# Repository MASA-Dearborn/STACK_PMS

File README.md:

# PMS
Power Management System board
STACK_PMS

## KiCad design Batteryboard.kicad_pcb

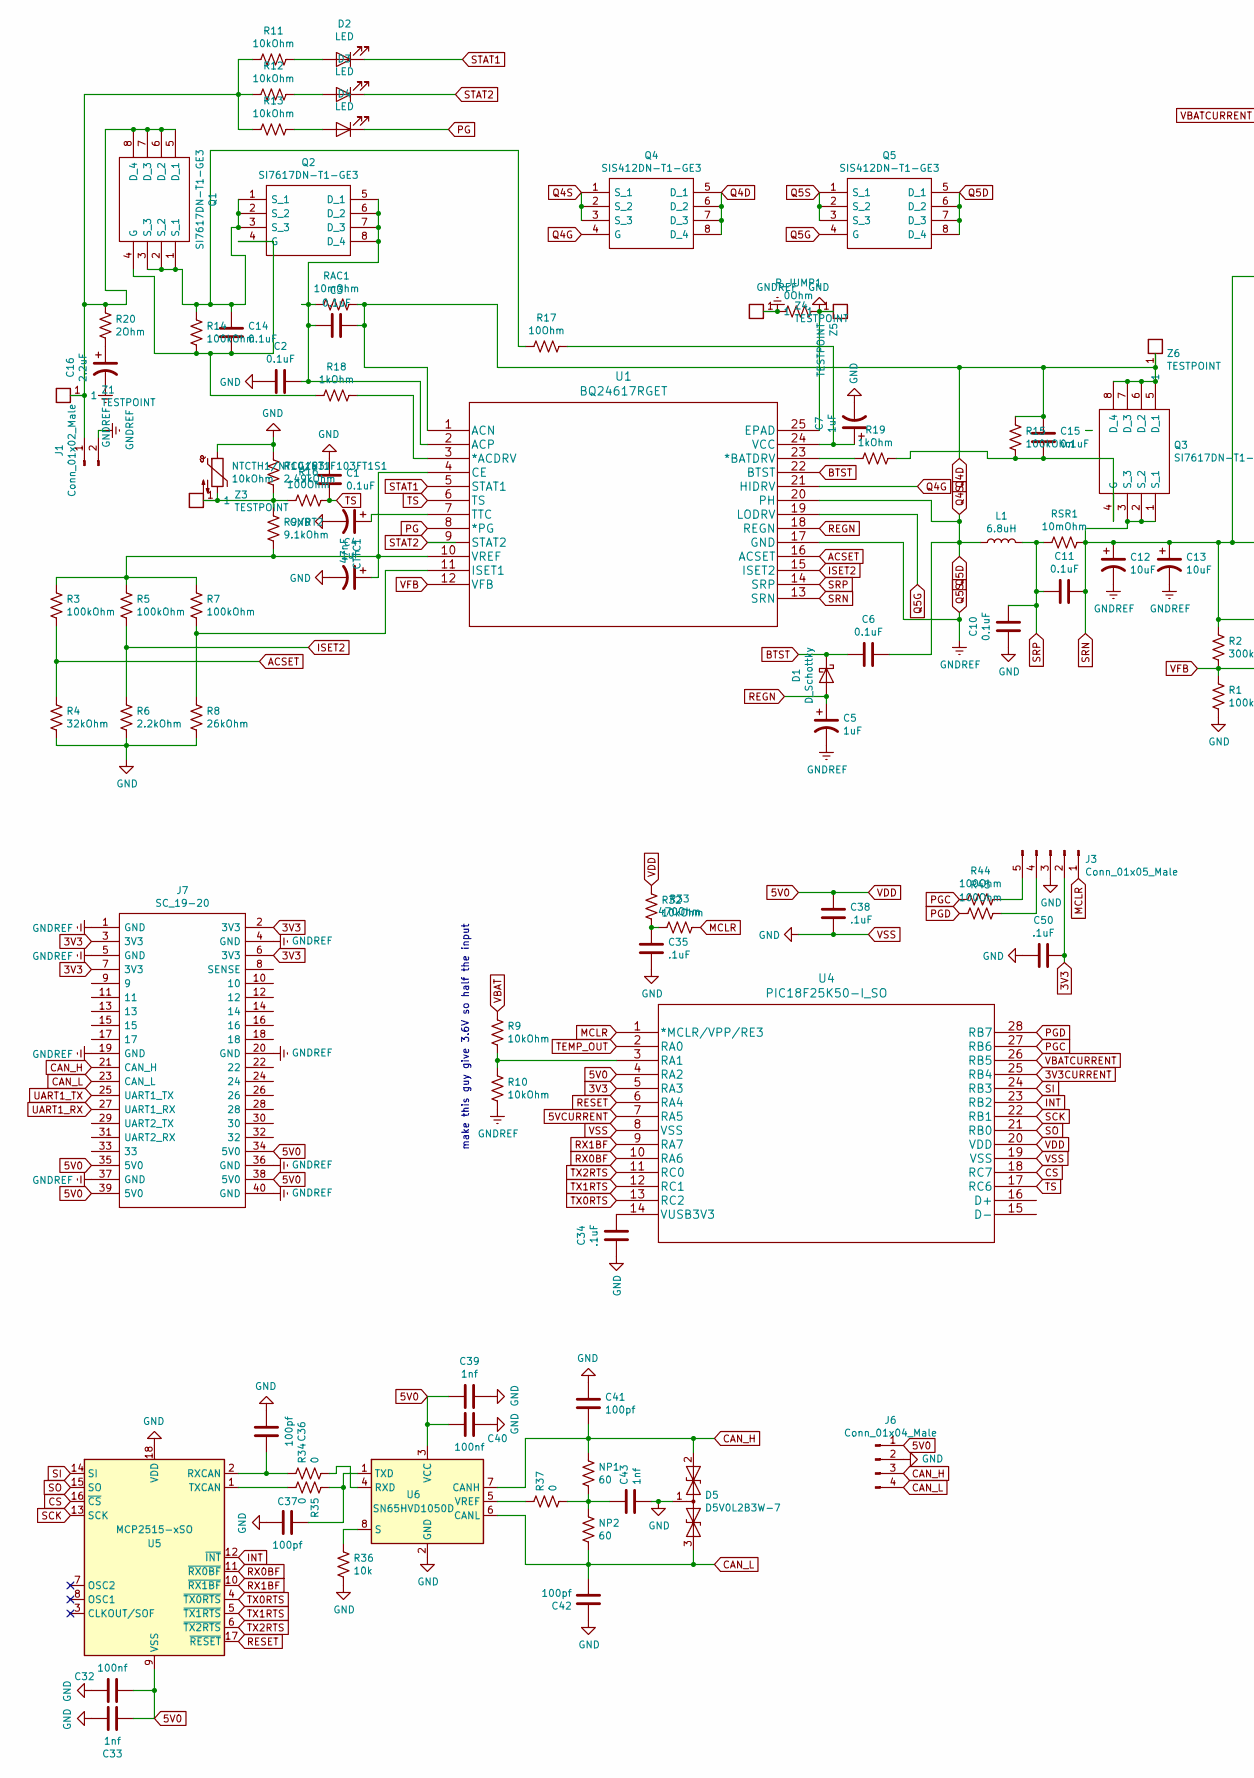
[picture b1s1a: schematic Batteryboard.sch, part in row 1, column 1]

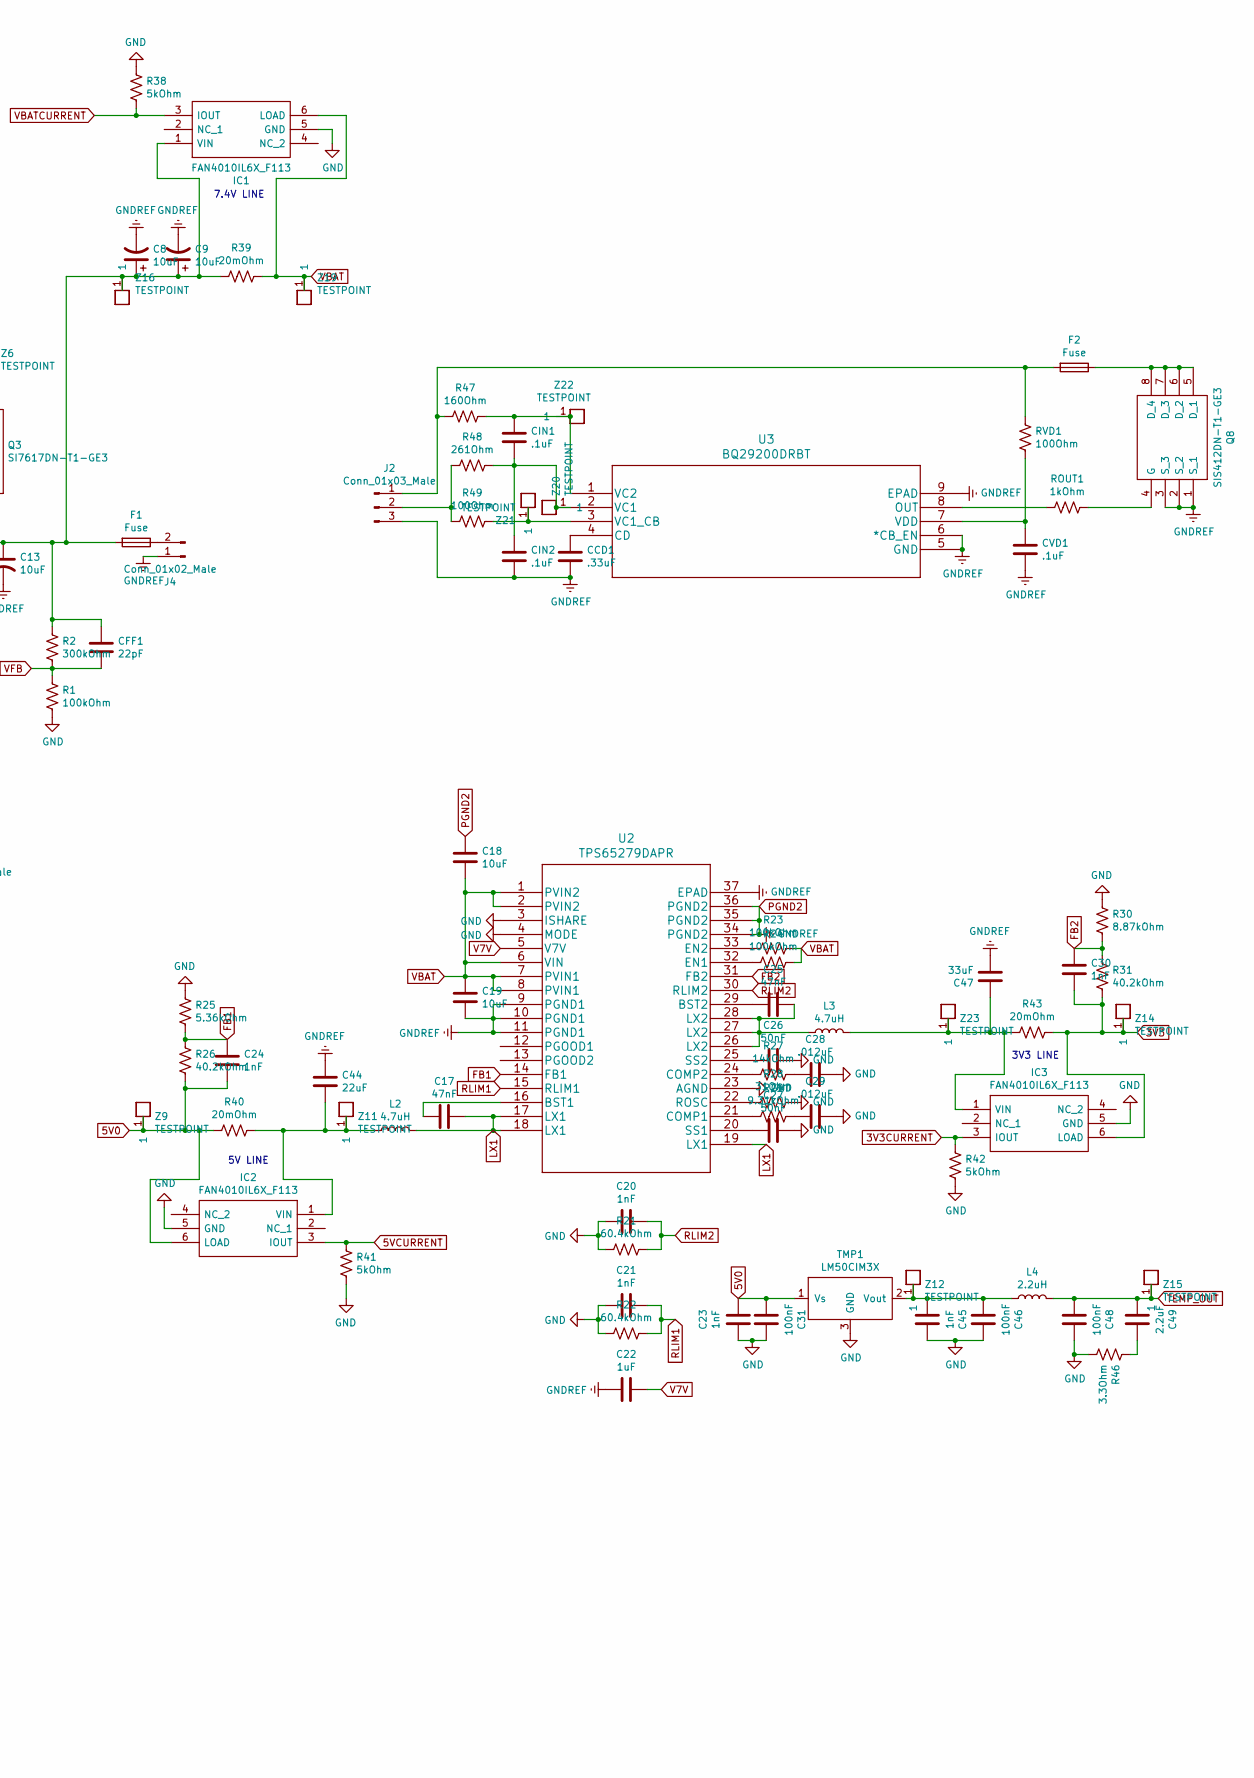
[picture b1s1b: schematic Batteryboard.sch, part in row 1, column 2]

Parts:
C1, C2, C3, C6, C10, C11, C14, C15: 0.1uF; C_0603_1608Metric
C4, C5, C7, C22: 1uF; C_0603_1608Metric
C8, C9, C12, C13, C18, C19: 10uF; C_0603_1608Metric
C16, C49: 2.2uF; C_0603_1608Metric
C17, C25: 47nF; C_0603_1608Metric
C20, C21, C23, C24, C30, C45: 1nF; C_0603_1608Metric
C26, C27: 50nF; C_0603_1608Metric
C28, C29: .012uF; C_0603_1608Metric
C31, C46, C48: 100nF; C_0603_1608Metric
C32, C40: 100nf; C_0603_1608Metric
C33, C39, C43: 1nf; C_0603_1608Metric
C34, C35, C38, C50: .1uF; C_0603_1608Metric
C36, C37, C41, C42: 100pf; C_0603_1608Metric
C44: 22uF; C_0603_1608Metric
C47: 33uF; C_0805_2012Metric
CCD1: .33uF; C_0603_1608Metric
CFF1: 22pF; C_0603_1608Metric
CIN1, CIN2: .1uF; C_0603_1608Metric
CTTC1: 47nF; C_0603_1608Metric
CVD1: .1uF; C_0603_1608Metric
D1: D_Schottky; D_SOD-323
D2, D3, D4: LED; D_0603_1608Metric
D5: D5V0L2B3W-7; SOT-23
F1, F2: Fuse; Fuseholder_Blade_Mini_Keystone_3557-2
IC1, IC2, IC3: FAN4010IL6X_F113; 6-LEAD_MICROPAK; Manufacturer_Part_Number FAN4010IL6X_F113; Mouser Part Number 512-FAN4010IL6X_F113
J1, J4: Conn_01x02_Male; 1-1123723-2
J2: Conn_01x03_Male; JST_XH_B3B-XH-AM_1x03_P2.50mm_Vertical
J3: Conn_01x05_Male; PinHeader_1x05_P2.54mm_Vertical
J6: Conn_01x04_Male; 1734595-4
J7: SC_19-20; Stack_Connector_2019_2020; Manufacturer_Part_Number TFC-120-32-F-D-A-K-TR
L1: 6.8uH; L_Vishay_IHLP-2525
L2, L3: 4.7uH; SRP7030-4R7M
L4: 2.2uH; L_0603_1608Metric
NP1, NP2: 60; R_0603_1608Metric
NTCTH1/NTCG163JF103FT1S1: 10kOhm; R_0603_1608Metric
Q1, Q2, Q3: SI7617DN-T1-GE3; SIS862DNT1GE3; Mouser Part Number 781-SI7617DN-GE3
Q4, Q5, Q8: SIS412DN-T1-GE3; SIS862DNT1GE3; Mouser Part Number 781-SI7617DN-GE3
R1, R3, R5, R7, R14, R15, R23, R24: 100kOhm; R_0603_1608Metric
R2: 300kOhm; R_0603_1608Metric
R4: 32kOhm; R_0603_1608Metric
R6: 2.2kOhm; R_0603_1608Metric
R8: 26kOhm; R_0603_1608Metric
R9, R10, R11, R12, R13, R32: 10kOhm; R_0603_1608Metric
R9/RT2: 9.1kOhm; R_0603_1608Metric
R10/RT1: 2.49kOhm; R_0603_1608Metric
R16, R44, R45, R49: 100Ohm; R_0603_1608Metric
R17: 10Ohm; R_0603_1608Metric
R18, R19: 1kOhm; R_0603_1608Metric
R20: 2Ohm; R_0603_1608Metric
R21, R22: 60.4kOhm; R_0603_1608Metric
R25: 5.36kOhm; R_0603_1608Metric
R26, R31: 40.2kOhm; R_0603_1608Metric
R27: 14kOhm; R_0603_1608Metric
R28: 31Ohm; R_0603_1608Metric
R29: 9.31kOhm; R_0603_1608Metric
R30: 8.87kOhm; R_0603_1608Metric
R33: 470Ohm; R_0603_1608Metric
R34, R35, R37: 0; R_0603_1608Metric
R36: 10k; R_0603_1608Metric
R38, R41, R42: 5kOhm; R_0603_1608Metric
R39, R40, R43: 20mOhm; R_0603_1608Metric
R46: 3.3Ohm; R_0603_1608Metric
R47: 160Ohm; R_0603_1608Metric
R48: 261Ohm; R_0603_1608Metric
RAC1: 10mOhm; R_0603_1608Metric
ROUT1: 1kOhm; R_0603_1608Metric
RSR1: 10mOhm; R_0603_1608Metric
RVD1: 100Ohm; R_0603_1608Metric
R_JUMP1: 0Ohm; R_0603_1608Metric
TMP1: LM50CIM3X; SOT-23
U1: BQ24617RGET
U2: TPS65279DAPR
U3: BQ29200DRBT
U4: PIC18F25K50-I_SO; PIC18F25K50-I&slash_SO
U5: MCP2515-xSO; SOIC-18W_7.5x11.6mm_P1.27mm
U6: SN65HVD1050D; SOIC-8_3.9x4.9mm_P1.27mm
Z1, Z3, Z4, Z5, Z6, Z9, Z11, Z12, Z14, Z15, Z16, Z19, Z20, Z21, Z22, Z23: TESTPOINT

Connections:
3V3: C30.2, C50.1, IC3.6 (LOAD), J3.2, J7.2 (3V3), J7.3 (3V3), J7.6 (3V3), J7.7 (3V3), R31.2, R43.1, U4.5 (RA3), Z14.1
3V3CURRENT: IC3.3 (IOUT), R42.1, U4.25 (RB4)
5V0: C23.1, C24.2, C31.2, C32.1, C33.2, C38.1, C39.2, C40.1, IC2.6 (LOAD), J6.1, J7.34 (5V0), J7.35 (5V0), J7.38 (5V0), J7.39 (5V0), R26.2, R32.1, R40.2, TMP1.1 (Vs), U4.4 (RA2), U4.20 (VDD), U5.9 (VSS), U6.3 (VCC), Z9.1
5VCURRENT: IC2.3 (IOUT), R41.1, U4.7 (RA5)
ACSET: R3.2, R4.1, U1.16 (ACSET)
BTST: C6.2, D1.1 (K), U1.22 (BTST)
CAN_H: C41.2, D5.2 (A1), J6.3, J7.21 (CAN_H), NP1.1, U6.7 (CANH)
CAN_L: C42.2, D5.3 (A2), J6.4, J7.23 (CAN_L), NP2.2, U6.6 (CANL)
CS: U4.18 (RC7), U5.16 (~CS)
FB1: C24.1, R25.2, R26.1, U2.14 (FB1)
FB2: C30.1, R30.2, R31.1, U2.31 (FB2)
INT: U4.23 (RB2), U5.12 (~INT)
ISET2: R5.2, R6.1, U1.15 (ISET2)
LX1: C17.1, L2.2, U2.17 (LX1), U2.18 (LX1), U2.19 (LX1)
MCLR: J3.1, R33.2, U4.1 (*MCLR/VPP/RE3)
unnamed: C2.1, C3.2, Q2.5 (D_1), Q2.6 (D_2), Q2.7 (D_3), Q2.8 (D_4), RAC1.2, U1.2 (ACP)
unnamed: C4.1, R3.1, R5.1, R7.1, R9/RT2.2, U1.4 (CE), U1.10 (VREF)
unnamed: C7.1, R17.1, U1.24 (VCC)
unnamed: C14.1, Q1.1 (S_1), Q1.2 (S_2), Q1.3 (S_3), Q2.1 (S_1), Q2.2 (S_2), Q2.3 (S_3), R14.1, R17.2
unnamed: C14.2, Q1.4 (G), Q2.4 (G), R14.2, R18.2
unnamed: C15.2, Q3.4 (G), R15.2, R19.1
unnamed: C16.1, R20.2
unnamed: C17.2, U2.16 (BST1)
unnamed: C25.1, L3.1, U2.26 (LX2), U2.27 (LX2), U2.28 (LX2)
unnamed: C25.2, U2.29 (BST2)
unnamed: C26.2, U2.25 (SS2)
unnamed: C27.2, U2.20 (SS1)
unnamed: C28.2, R27.1
unnamed: C29.2, R29.1
unnamed: C34.2, U4.14 (VUSB3V3)
unnamed: C35.1, R32.2, R33.1
unnamed: C36.1, R34.1, U5.2 (RXCAN)
unnamed: C37.2, R35.1, U6.1 (TXD)
unnamed: C43.1, NP1.2, NP2.1, R37.2
unnamed: C44.2, IC2.1 (VIN), L2.1, R40.1, Z11.1
unnamed: C45.2, C46.2, L4.1, TMP1.2 (Vout), Z12.1
unnamed: C47.1, IC3.1 (VIN), L3.2, R43.2, Z23.1
unnamed: C49.1, R46.1
unnamed: CCD1.1, U3.4 (CD)
unnamed: CIN1.1, R47.1, U3.1 (VC2), Z22.1
unnamed: CIN1.2, CIN2.1, R48.1, U3.2 (VC1), Z20.1
unnamed: CTTC1.1, U1.7 (TTC)
unnamed: CVD1.1, RVD1.2, U3.7 (VDD)
unnamed: D2.2 (A), R11.1
unnamed: D3.2 (A), R12.1
unnamed: D4.2 (A), R13.1
unnamed: F1.1, J4.2
unnamed: F2.1, Q8.5 (D_1), Q8.6 (D_2), Q8.7 (D_3), Q8.8 (D_4)
unnamed: F2.2, J2.1, R47.2, RVD1.1
unnamed: J1.1, Q1.5 (D_1), Q1.6 (D_2), Q1.7 (D_3), Q1.8 (D_4), R11.2, R12.2, R13.2, R20.1, Z1.1
unnamed: J2.2, R48.2, R49.2
unnamed: J3.4, R45.2
unnamed: J3.5, R44.1
unnamed: NTCTH1/NTCG163JF103FT1S1.2, R9/RT2.1, R10/RT1.2, R16.2, Z3.1
unnamed: Q8.4 (G), ROUT1.1
unnamed: R7.2, R8.1, U1.11 (ISET1)
unnamed: R9.2, R10.1, U4.3 (RA1)
unnamed: R18.1, U1.3 (*ACDRV)
unnamed: R19.2, U1.23 (*BATDRV)
unnamed: R23.2, U2.33 (EN2)
unnamed: R24.2, U2.32 (EN1)
unnamed: R27.2, U2.24 (COMP2)
unnamed: R28.2, U2.22 (ROSC)
unnamed: R29.2, U2.21 (COMP1)
unnamed: R34.2, U6.4 (RXD)
unnamed: R35.2, U5.1 (TXCAN)
unnamed: R36.1, U6.8 (S)
unnamed: R37.1, U6.5 (VREF)
unnamed: R49.1, U3.3 (VC1_CB), Z21.1
unnamed: ROUT1.2, U3.8 (OUT)
PG: D4.1 (K), U1.8 (*PG)
PGC: R44.2, U4.27 (RB6)
PGD: R45.1, U4.28 (RB7)
PGND2: C5.2, C8.2, C9.2, C12.2, C13.2, C16.2, C18.1, C19.2, C22.2, C44.1, C47.2, CCD1.2, CIN2.2, CVD1.2, J1.2, J2.3, J4.1, J7.1 (GND), J7.4 (GND), J7.5 (GND), J7.19 (GND), J7.20 (GND), J7.36 (GND), J7.37 (GND), J7.40 (GND), Q5.1 (S_1), Q5.2 (S_2), Q5.3 (S_3), Q8.1 (S_1), Q8.2 (S_2), Q8.3 (S_3), R10.2, R_JUMP1.2, U1.17 (GND), U2.9 (PGND1), U2.10 (PGND1), U2.11 (PGND1), U2.34 (PGND2), U2.35 (PGND2), U2.36 (PGND2), U2.37 (EPAD), U3.5 (GND), U3.6 (*CB_EN), U3.9 (EPAD), Z4.1
Q4D: C3.1, C15.1, Q3.5 (D_1), Q3.6 (D_2), Q3.7 (D_3), Q3.8 (D_4), Q4.5 (D_1), Q4.6 (D_2), Q4.7 (D_3), Q4.8 (D_4), R15.1, RAC1.1, U1.1 (ACN), Z6.1
Q4G: Q4.4 (G), U1.21 (HIDRV)
Q4S: C6.1, L1.1, Q4.1 (S_1), Q4.2 (S_2), Q4.3 (S_3), Q5.5 (D_1), Q5.6 (D_2), Q5.7 (D_3), Q5.8 (D_4), U1.20 (PH)
Q5G: Q5.4 (G), U1.19 (LODRV)
REGN: C5.1, D1.2 (A), U1.18 (REGN)
RESET: U4.6 (RA4), U5.17 (~RESET)
RLIM1: C21.1, R22.1, U2.15 (RLIM1)
RLIM2: C20.1, R21.1, U2.30 (RLIM2)
RX0BF: U4.10 (RA6), U5.11 (~RX0BF)
RX1BF: U4.9 (RA7), U5.10 (~RX1BF)
SCK: U4.22 (RB1), U5.13 (SCK)
SI: U4.24 (RB3), U5.14 (SI)
SO: U4.21 (RB0), U5.15 (SO)
SRN: C8.1, C9.1, C11.1, C12.1, C13.1, CFF1.1, F1.2, IC1.1 (VIN), Q3.1 (S_1), Q3.2 (S_2), Q3.3 (S_3), R2.1, R39.2, RSR1.1, U1.13 (SRN), Z16.1
SRP: C10.1, C11.2, L1.2, RSR1.2, U1.14 (SRP)
STAT1: D2.1 (K), U1.5 (STAT1)
STAT2: D3.1 (K), U1.9 (STAT2)
TEMP_OUT: C48.2, C49.2, L4.2, U4.2 (RA0), Z15.1
TS: C1.2, R16.1, U1.6 (TS), U4.17 (RC6)
TX0RTS: U4.13 (RC2), U5.4 (~TX0RTS)
TX1RTS: U4.12 (RC1), U5.5 (~TX1RTS)
TX2RTS: U4.11 (RC0), U5.6 (~TX2RTS)
V7V: C22.1, U2.5 (V7V)
VBAT: C18.2, C19.1, IC1.6 (LOAD), R9.1, R23.1, R24.1, R39.1, U2.1 (PVIN2), U2.2 (PVIN2), U2.6 (VIN), U2.7 (PVIN1), U2.8 (PVIN1), Z19.1
VBATCURRENT: IC1.3 (IOUT), R38.2, U4.26 (RB5)
VFB: CFF1.2, R1.1, R2.2, U1.12 (VFB)
VSS: C1.1, C2.2, C4.2, C7.2, C10.2, C20.2, C21.2, C23.2, C26.1, C27.1, C28.1, C29.1, C31.1, C32.2, C33.1, C34.1, C35.2, C36.2, C37.1, C38.2, C39.1, C40.2, C41.1, C42.1, C43.2, C45.1, C46.1, C48.1, C50.2, CTTC1.2, D5.1 (common), IC1.5 (GND), IC2.5 (GND), IC3.5 (GND), J3.3, J6.2, NTCTH1/NTCG163JF103FT1S1.1, R1.2, R4.2, R6.2, R8.2, R10/RT1.1, R21.2, R22.2, R25.1, R28.1, R30.1, R36.2, R38.1, R41.2, R42.2, R46.2, R_JUMP1.1, TMP1.3 (GND), U1.25 (EPAD), U2.3 (ISHARE), U2.4 (MODE), U2.23 (AGND), U4.8 (VSS), U4.19 (VSS), U5.18 (VDD), U6.2 (GND), Z5.1

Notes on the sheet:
3V3 LINE
5V LINE
make this guy give 3.6V so half the input
7.4V LINE

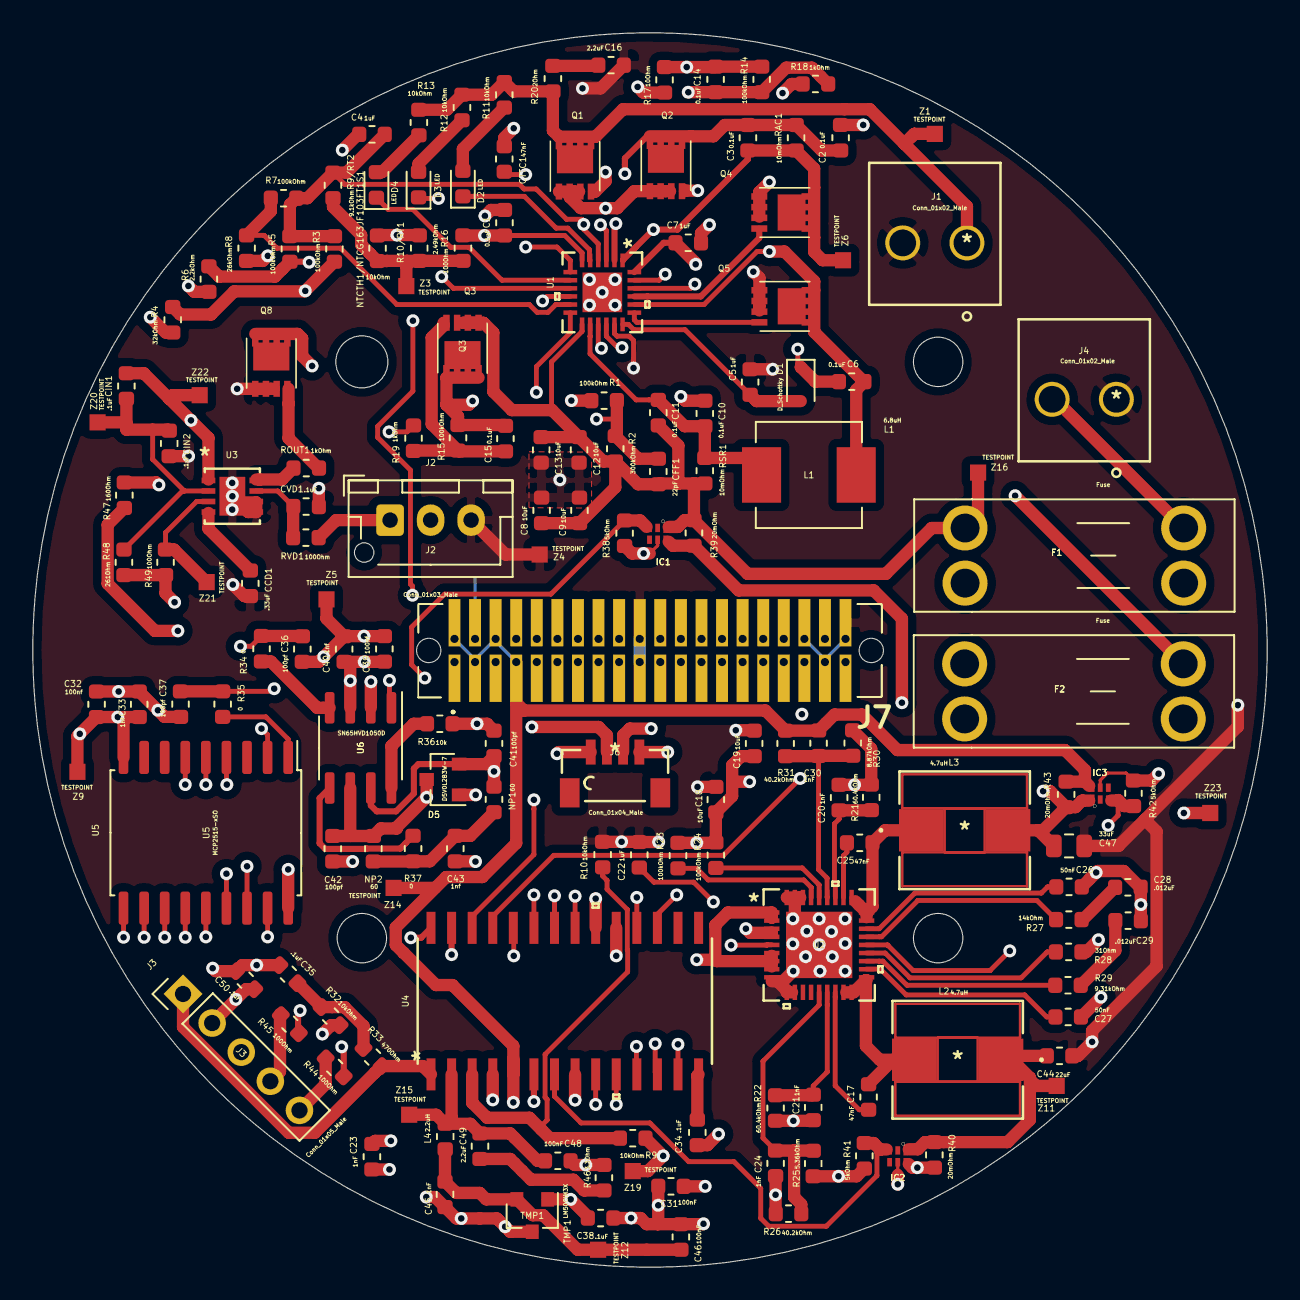
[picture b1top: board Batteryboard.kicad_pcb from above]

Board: 4 copper layers, 76.2 x 76.2 mm, 164 parts (1 on the bottom side), 101 nets.

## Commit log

2019-11-20 Silkscreen Fixed
2019-11-21 Didn't save schematic
2019-12-22 Final PMS test board, ready for Stefka, and then printing
2019-12-24 first commit, board still has a ways to go
2019-12-24 first commit, still have a way to go
2019-12-25 made lots of progress schematic wise, still need to add a few things to be sure, but its progress
2019-12-27 more progress on the way to being done, added a bunch of stuff having to do with current sense
2019-12-29 finished schematic, more or less
2019-12-30 made progress on layout, charging IC is basically done
2019-12-30 added in layout for battery balancing IC
2019-12-31 added layout for buck converter
2020-01-01 got all components on there, routing and grounding to do still
2020-01-02 routing done, need to figure out grounding everything still
2020-01-12 complete overhaul of board, trying to make it a bit better
2020-01-12 finished for the night, 80 something traces left, then onto implementing proper grounding, which should be easy given that I have a huge uninterrupted ground plane to work with
2020-01-13 finished rotuing all my traces, grounding next
2020-01-13 grounded everything, hopefully well, but that is not a guarantee
2020-01-14 fixed current sense ICs
2020-01-22 fixed some stuff, grounding and a few traces
2020-01-22 fixed another little trace
2020-01-30 big overhaul on board, did a bunch of stuff
2020-02-02 basically an emergency backup, going to reroute my board
2020-02-02 here u go matt, thanks for helping make this bomb
2020-02-02 Fixed CAN resistors and added filtering
2020-02-03 schematic is final now, working on routing my board again
2020-02-04 did my board again, heck yeah, actually quite happy with it this time
2020-02-07 added 4 pin for AOA sensor
2020-02-08 made lots of progress on silkscreen, and fixed some jank with values
2020-02-08 board is actually done?
2020-02-09 k its like super done this time
2020-02-09 fixed silkscreen up more
2020-02-09 there was 1 more resistor needed fixed
2020-02-09 Fixed silk screen
2020-02-11 addede pms silkscreen
2020-02-18 changed up balancing circuit cuz that no work and that bad
2020-02-18 made some finishing touches, should be complete now
2020-02-19 fixed stuff
2020-02-20 fixed some shit
2020-02-20 added ground pours

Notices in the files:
parts and their libraries:
Copyright 2016 Accelerated Designs. All rights reserved.
